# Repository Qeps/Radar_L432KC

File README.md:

# Doppler Radar Processing on STM32 (FreeRTOS)

## Overview

This project implements a **real-time Doppler radar signal processing pipeline** on an **STM32L432KC** microcontroller using **FreeRTOS**.

The system continuously acquires analog radar signals using **ADC with DMA**, dispatches buffer-ready events in a lightweight real-time task, performs signal processing in a dedicated DSP task, and outputs results asynchronously over **UART**.  
End-to-end latency and **deadline misses are explicitly monitored and reported**, making real-time behavior observable.

The project focuses on **correct RTOS architecture**, deterministic behavior, and clear separation of responsibilities rather than raw signal-processing complexity.

---

## Architecture

- ADC + DMA (circular buffer)
- DMA ISR (half / full buffer)
- Dispatch Task
- DSP Processing Task
- FreeRTOS Queues
- UART Task
- Serial Output

### Key Design Choices

- Continuous ADC sampling using DMA (no CPU polling)
- Event-driven task activation via DMA interrupts
- Separation of real-time processing and I/O
- Explicit timing model with deadline detection
- No dynamic memory allocation at runtime

---

## FreeRTOS Tasks

### Dispatch Task

- Triggered by ADC DMA half/full completion
- Selects the active ADC buffer half
- Submits DSP jobs via a queue
- Acts as the timing reference
- Does not perform signal processing

### DSP Processing Task

- Blocks on a DSP job queue
- Processes one buffer half per activation
- Performs motion detection and speed estimation
- Reports results and deadline violations

### UART Task

- Receives messages via a queue
- Formats and sends output over UART
- Fully isolated from real-time constraints

---

## Inter-Task Communication

Tasks communicate using **two FreeRTOS queues**:

- DSP queue for buffer pointers and timing metadata
- UART queue for tagged output messages

```c
typedef enum {
    MSG_RESULT,
    MSG_DEADLINE,
    MSG_WARN
} uart_msg_type_t;

typedef struct {
    uart_msg_type_t type;
    union {
        motion_result_t result;
        struct {
            uint32_t miss_cnt;
            uint32_t exec_ms;
        } deadline;
        struct {
            uint32_t code;
        } warn;
    } u;
} uart_msg_t;
```
This keeps the UART task simple and allows reporting results, deadline violations, and warnings without impacting real-time behavior.

---

## Signal Processing
For each ADC buffer half:
- DC offset removal (mean subtraction)
- Peak-to-peak amplitude calculation
- Motion detection using amplitude threshold
- Speed estimation using zero-crossing based Doppler frequency
The algorithm is intentionally simple and deterministic, prioritizing predictable execution time.

---

## Timing and Real-Time Behavior
- Processing is triggered by ADC DMA events
- End-to-end dispatch-to-DSP latency is measured using RTOS ticks
- Deadline misses are detected and reported over UART
Example output:
```bash
amp_pp=689.0 motion=1 speed=0.89 m/s
DEADLINE MISS: cnt=145 latency=128 ms
```
This makes timing behavior explicit and debuggable.

---

## Why This Is an RTOS Project
- Asynchronous data acquisition (ADC + DMA)
- Event-driven task execution
- Clear task priorities and isolation
- Deterministic inter-task communication
- Measured and reported timing constraints

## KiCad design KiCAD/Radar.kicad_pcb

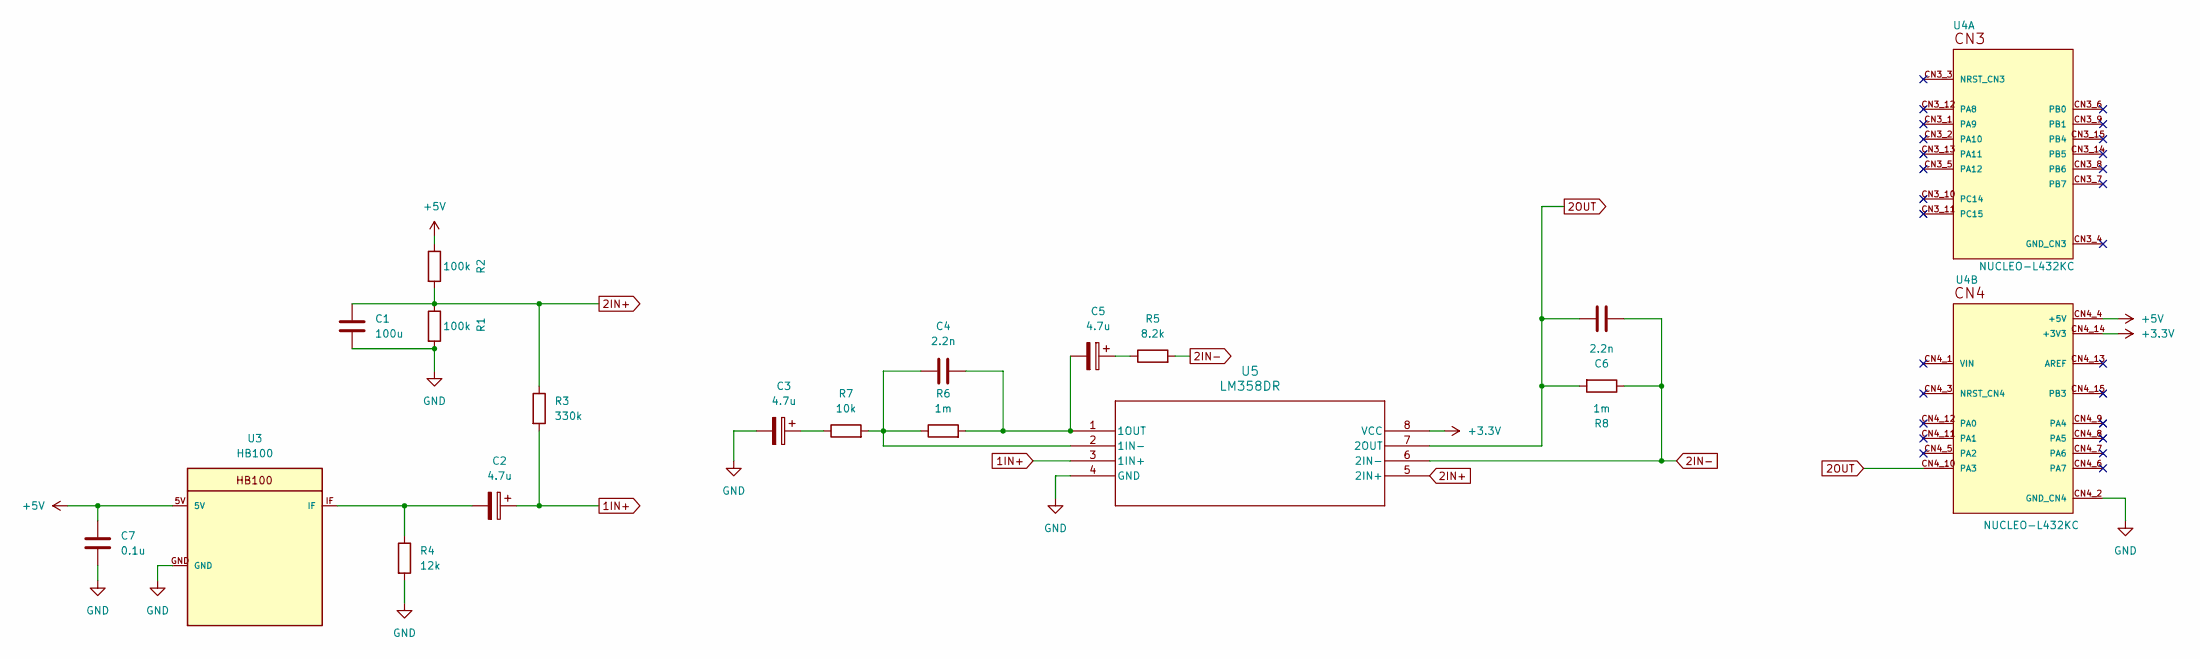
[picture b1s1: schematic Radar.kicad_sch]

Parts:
C1: 100u; C_0603_1608Metric_Pad1.08x0.95mm_HandSolder
C2, C3, C5: 4.7u; CP_Elec_4x5.4
C4, C6: 2.2n; C_0603_1608Metric_Pad1.08x0.95mm_HandSolder
C7: 0.1u; C_0603_1608Metric_Pad1.08x0.95mm_HandSolder
R1, R2: 100k; R_0603_1608Metric_Pad0.98x0.95mm_HandSolder
R3: 330k; R_0603_1608Metric_Pad0.98x0.95mm_HandSolder
R4: 12k; R_0603_1608Metric_Pad0.98x0.95mm_HandSolder
R5: 8.2k; R_0603_1608Metric_Pad0.98x0.95mm_HandSolder
R6, R8: 1m; R_0603_1608Metric_Pad0.98x0.95mm_HandSolder
R7: 10k; R_0603_1608Metric_Pad0.98x0.95mm_HandSolder
U3: HB100
U4: NUCLEO-L432KC; MODULE_NUCLEO-L432KC; PARTREV N/A
U5: LM358DR; D8

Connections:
1IN+: C2.1, R3.2, U5.3 (1IN+)
2IN+: C1.1, R1.1, R2.2, R3.1, U5.5 (2IN+)
2IN-: C6.1, R5.2, R8.1, U5.6 (2IN-)
2OUT: C6.2, R8.2, U4.CN4_10 (PA3), U5.7 (2OUT)
+3.3V: U4.CN4_14 (+3V3), U5.8 (VCC)
+5V: C7.1, R2.1, U3.5V, U4.CN4_4 (+5V)
GND: C1.2, C3.2, C7.2, R1.2, R4.2, U3.GND, U4.CN4_2 (GND_CN4), U5.4 (GND)
unnamed: C2.2, R4.1, U3.IF
unnamed: C3.1, R7.1
unnamed: C5.1, R5.1
unnamed: C4.1, R6.1, R7.2, U5.2 (1IN-)
unnamed: C4.2, C5.2, R6.2, U5.1 (1OUT)

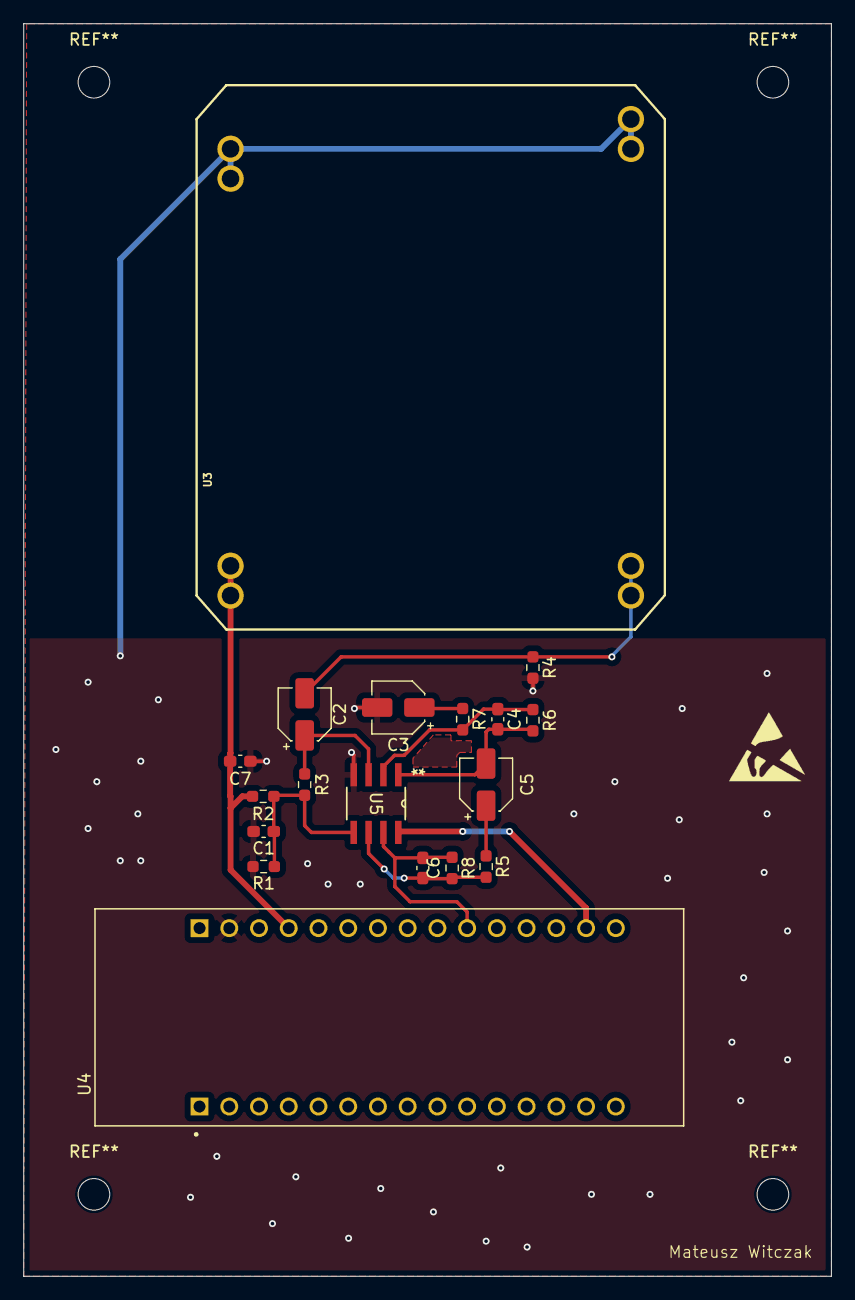
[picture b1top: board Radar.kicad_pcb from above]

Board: 2 copper layers, 69.0 x 107.0 mm, 18 parts (0 on the bottom side), 12 nets.

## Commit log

2025-10-28 Folder name change
2025-10-28 ninja commit
2025-10-29 Layout update
2025-10-29 added components values
2025-10-29 Layout V1
2025-10-29 Layout V2
2025-10-30 PCB V1
2025-10-30 PCB V2
2025-10-30 PCB V3
2025-10-30 PCB V4
2025-11-02 Base STM32 freeRTOS project, TIM6 instead SysTick, newlib reentrant enable
2025-11-03 PCB V5
2025-11-03 PCB final version
2025-11-04 Final PCB update
2025-11-09 Example of task creation, task handler using freeRTOS api, without CMSIS_V2 interface
2025-11-17 3D visualization update
2025-11-30 HAL TIM1->ADC1->DMA test - buffer is filled with data
2025-12-23 Add no-CMSIS freeRTOS api, ADC+DMA+tasks test approved
2026-01-18 Added simulation of HB100 on Nucleo F303RE - DAC+DMA config
2026-01-18 Added matlab file - generating samples for HB100 simulation and results plots
2026-01-20 Added 1 kHz ADC sampling (TIM1), static 256-sample ADC DMA buffer for motion detection and speed estimation
2026-01-20 Fix htim1.Init.Prescaler -> 1000 Hz
2026-01-20 Added ADC DMA motion detection and Doppler speed estimation task (work in progress)
2026-01-23 Fixed timer prescaler for DAC
2026-01-23 Fixed motion detection and Doppler speed estimation task (UART debug, results are consistent with MATLAB.)
2026-01-23 Added FreeRTOS task notifications for ADC DMA events and fix ISR priority. Replaced polling and global flags with direct-to-task notifications and xTaskNotifyWait. Lowered DMA/ADC interrupt priority 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
2026-01-23 Separate motion processing and UART output into two FreeRTOS tasks using a queue. Motion task produces measurement results, UART task consumes and transmits them, avoiding blocking I/O in the process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
2026-01-23 Added periodic motion task with execution time measurement and deadline miss detection
2026-01-23 Adjust motion task deadline to 150 ms to reflect full ADC/DMA buffer latency
2026-01-23 Fix comment
2026-01-24 Refactor motion processing into dispatcher-DSP task split with RTOS scheduling
2026-01-24 Updated README, test delay for projects testing need
